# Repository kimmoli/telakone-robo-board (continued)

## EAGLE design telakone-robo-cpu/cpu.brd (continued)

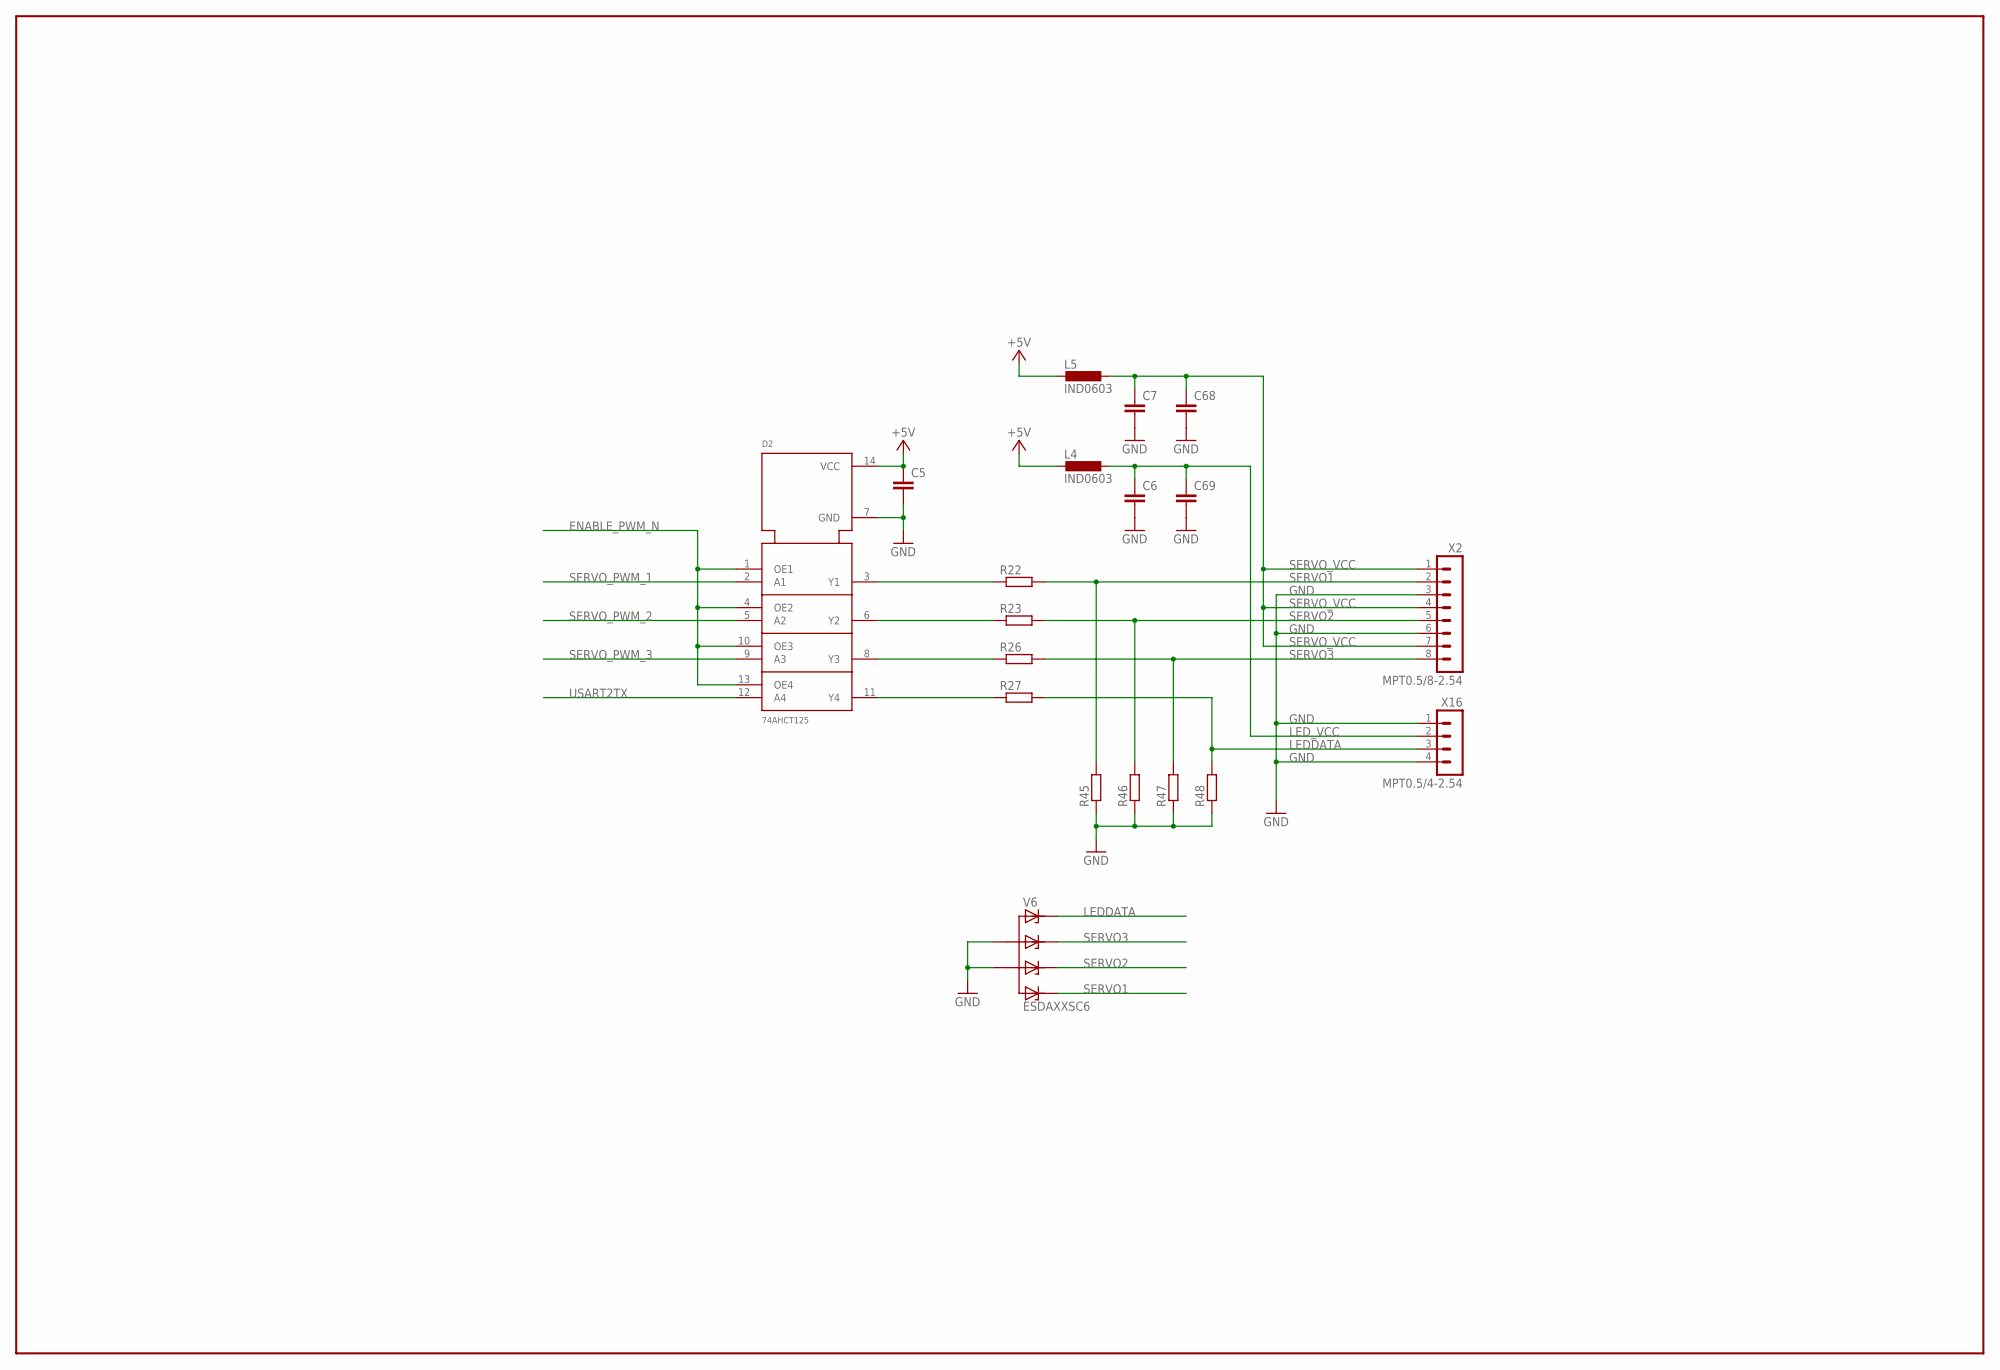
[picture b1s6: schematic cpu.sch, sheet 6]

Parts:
C5: CAP0603; OMAT_IC_2_C0603
C6, C7, C68, C69: CAP0805; OMAT_IC_2_C0805
D2: 74AHCT125; SO14
L4, L5: IND0603; OMAT_IC_2_R0603
R22, R23, R26, R27, R45, R46, R47, R48: RES0603; OMAT_IC_2_R0603
V6: ESDAXXSC6; OMAT_IC_2_SOT23-6
X2: MPT0.5/8-2.54; OMAT_IC_2_MPT0.5/8-2.54
X16: MPT0.5/4-2.54

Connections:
+5V: C5.1, D2.14 (VCC), L4.2, L5.2; also elsewhere on the board
ENABLE_PWM_N: D2.1 (OE1), D2.4 (OE2), D2.10 (OE3), D2.13 (OE4); also elsewhere on the board
GND: C5.2, C6.2, C7.2, C68.2, C69.2, D2.7 (GND), R45.1, R46.1, R47.1, R48.1, V6.2 (A), V6.5 (A1), X2.3, X2.6, X16.1, X16.4; also elsewhere on the board
LEDDATA: R27.2, R48.2, V6.1 (C), X16.3
LED_VCC: C6.1, C69.1, L4.1, X16.2
unnamed: D2.3 (Y1), R22.1
unnamed: D2.6 (Y2), R23.1
unnamed: D2.8 (Y3), R26.1
unnamed: D2.11 (Y4), R27.1
SERVO1: R22.2, R45.2, V6.6 (C3), X2.2
SERVO2: R23.2, R46.2, V6.4 (C2), X2.5
SERVO3: R26.2, R47.2, V6.3 (C1), X2.8
SERVO_PWM_1: D2.2 (A1); also elsewhere on the board
SERVO_PWM_2: D2.5 (A2); also elsewhere on the board
SERVO_PWM_3: D2.9 (A3); also elsewhere on the board
SERVO_VCC: C7.1, C68.1, L5.1, X2.1, X2.4, X2.7
USART2TX: D2.12 (A4); also elsewhere on the board

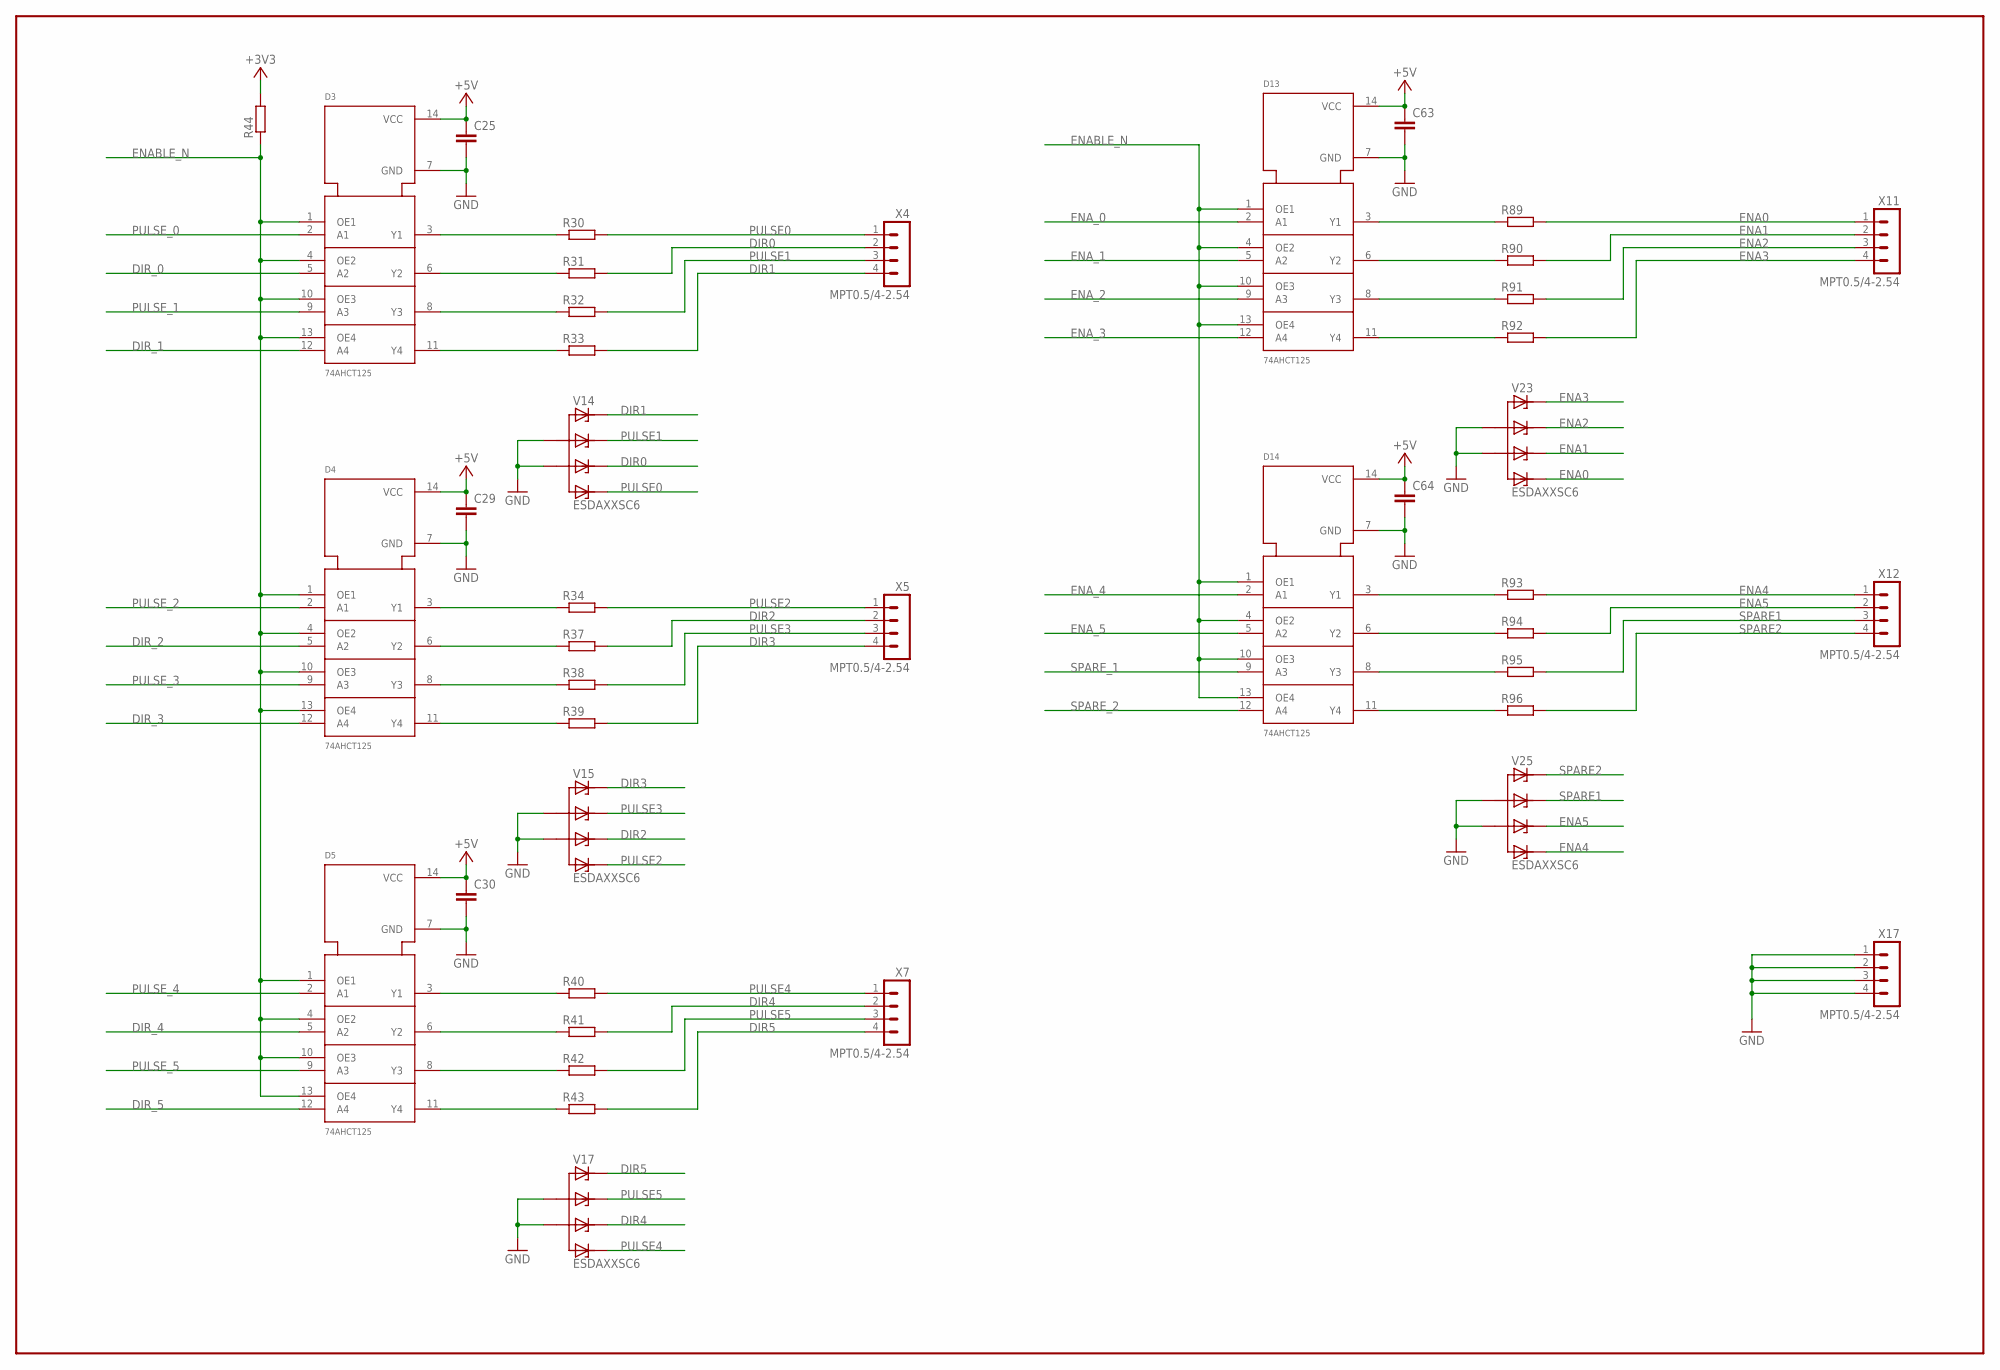
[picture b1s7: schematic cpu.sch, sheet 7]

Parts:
C25, C29, C30, C63, C64: CAP0603; OMAT_IC_2_C0603
D3, D4, D5, D13, D14: 74AHCT125; SO14
R30, R31, R32, R33, R34, R37, R38, R39, R40, R41, R42, R43, R44, R89, R90, R91, R92, R93, R94, R95, R96: RES0603; OMAT_IC_2_R0603
V14, V15, V17, V23, V25: ESDAXXSC6; OMAT_IC_2_SOT23-6
X4, X5, X7, X11, X12, X17: MPT0.5/4-2.54

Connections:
+3V3: R44.2; also elsewhere on the board
+5V: C25.1, C29.1, C30.1, C63.1, C64.1, D3.14 (VCC), D4.14 (VCC), D5.14 (VCC), D13.14 (VCC), D14.14 (VCC); also elsewhere on the board
DIR0: R31.2, V14.4 (C2), X4.2
DIR1: R33.2, V14.1 (C), X4.4
DIR2: R37.2, V15.4 (C2), X5.2
DIR3: R39.2, V15.1 (C), X5.4
DIR4: R41.2, V17.4 (C2), X7.2
DIR5: R43.2, V17.1 (C), X7.4
DIR_0: D3.5 (A2); also elsewhere on the board
DIR_1: D3.12 (A4); also elsewhere on the board
DIR_2: D4.5 (A2); also elsewhere on the board
DIR_3: D4.12 (A4); also elsewhere on the board
DIR_4: D5.5 (A2); also elsewhere on the board
DIR_5: D5.12 (A4); also elsewhere on the board
ENA0: R89.2, V23.6 (C3), X11.1
ENA1: R90.2, V23.4 (C2), X11.2
ENA2: R91.2, V23.3 (C1), X11.3
ENA3: R92.2, V23.1 (C), X11.4
ENA4: R93.2, V25.6 (C3), X12.1
ENA5: R94.2, V25.4 (C2), X12.2
ENABLE_N: D3.1 (OE1), D3.4 (OE2), D3.10 (OE3), D3.13 (OE4), D4.1 (OE1), D4.4 (OE2), D4.10 (OE3), D4.13 (OE4), D5.1 (OE1), D5.4 (OE2), D5.10 (OE3), D5.13 (OE4), D13.1 (OE1), D13.4 (OE2), D13.10 (OE3), D13.13 (OE4), D14.1 (OE1), D14.4 (OE2), D14.10 (OE3), D14.13 (OE4), R44.1; also elsewhere on the board
ENA_0: D13.2 (A1); also elsewhere on the board
ENA_1: D13.5 (A2); also elsewhere on the board
ENA_2: D13.9 (A3); also elsewhere on the board
ENA_3: D13.12 (A4); also elsewhere on the board
ENA_4: D14.2 (A1); also elsewhere on the board
ENA_5: D14.5 (A2); also elsewhere on the board
GND: C25.2, C29.2, C30.2, C63.2, C64.2, D3.7 (GND), D4.7 (GND), D5.7 (GND), D13.7 (GND), D14.7 (GND), V14.2 (A), V14.5 (A1), V15.2 (A), V15.5 (A1), V17.2 (A), V17.5 (A1), V23.2 (A), V23.5 (A1), V25.2 (A), V25.5 (A1), X17.1, X17.2, X17.3, X17.4; also elsewhere on the board
unnamed: D3.3 (Y1), R30.1
unnamed: D3.6 (Y2), R31.1
unnamed: D3.8 (Y3), R32.1
unnamed: D3.11 (Y4), R33.1
unnamed: D4.3 (Y1), R34.1
unnamed: D4.6 (Y2), R37.1
unnamed: D4.8 (Y3), R38.1
unnamed: D4.11 (Y4), R39.1
unnamed: D5.3 (Y1), R40.1
unnamed: D5.6 (Y2), R41.1
unnamed: D5.8 (Y3), R42.1
unnamed: D5.11 (Y4), R43.1
unnamed: D13.3 (Y1), R89.1
unnamed: D13.6 (Y2), R90.1
unnamed: D13.8 (Y3), R91.1
unnamed: D13.11 (Y4), R92.1
unnamed: D14.3 (Y1), R93.1
unnamed: D14.6 (Y2), R94.1
unnamed: D14.8 (Y3), R95.1
unnamed: D14.11 (Y4), R96.1
PULSE0: R30.2, V14.6 (C3), X4.1
PULSE1: R32.2, V14.3 (C1), X4.3
PULSE2: R34.2, V15.6 (C3), X5.1
PULSE3: R38.2, V15.3 (C1), X5.3
PULSE4: R40.2, V17.6 (C3), X7.1
PULSE5: R42.2, V17.3 (C1), X7.3
PULSE_0: D3.2 (A1); also elsewhere on the board
PULSE_1: D3.9 (A3)
PULSE_2: D4.2 (A1); also elsewhere on the board
PULSE_3: D4.9 (A3); also elsewhere on the board
PULSE_4: D5.2 (A1); also elsewhere on the board
PULSE_5: D5.9 (A3); also elsewhere on the board
SPARE1: R95.2, V25.3 (C1), X12.3
SPARE2: R96.2, V25.1 (C), X12.4
SPARE_1: D14.9 (A3); also elsewhere on the board
SPARE_2: D14.12 (A4); also elsewhere on the board

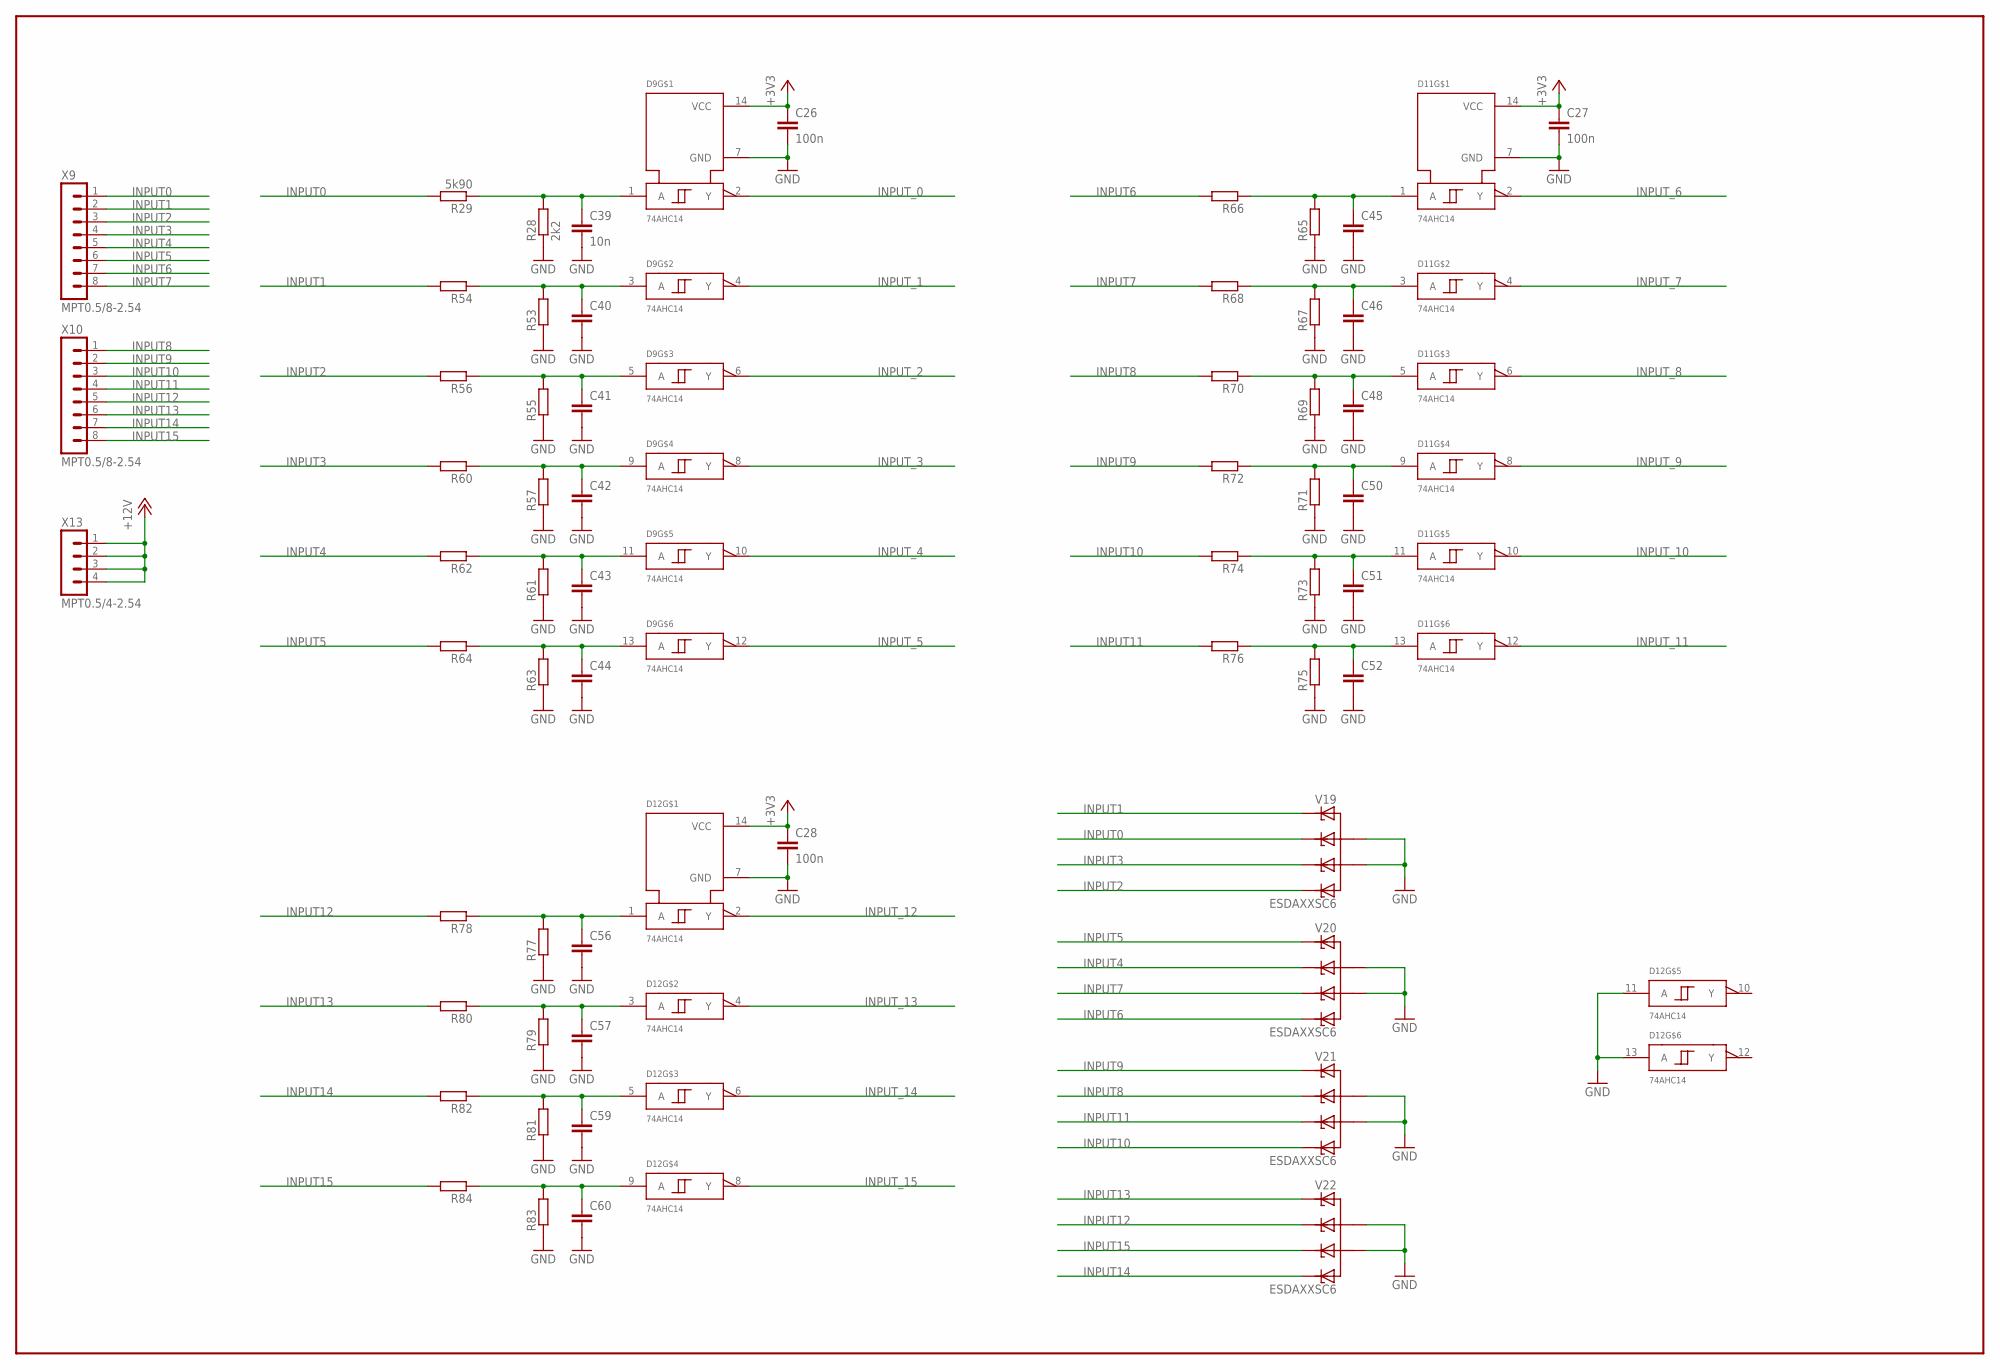
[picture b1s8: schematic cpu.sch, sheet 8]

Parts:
C26, C27, C28: 100n; C0603
C39: 10n; OMAT_IC_2_C0603
C40, C41, C42, C43, C44, C45, C46, C48, C50, C51, C52, C56, C57, C59, C60: CAP0603; OMAT_IC_2_C0603
D9, D11, D12: 74AHC14; SO14
R28: 2k2; OMAT_IC_2_R0603
R29: 5k90; OMAT_IC_2_R0603
R53, R54, R55, R56, R57, R60, R61, R62, R63, R64, R65, R66, R67, R68, R69, R70, R71, R72, R73, R74, R75, R76, R77, R78, R79, R80, R81, R82, R83, R84: RES0603; OMAT_IC_2_R0603
V19, V20, V21, V22: ESDAXXSC6; OMAT_IC_2_SOT23-6
X9, X10: MPT0.5/8-2.54; OMAT_IC_2_MPT0.5/8-2.54
X13: MPT0.5/4-2.54

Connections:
+3V3: C26.1, C27.1, C28.1, D9.14 (VCC), D11.14 (VCC), D12.14 (VCC); also elsewhere on the board
+12V: X13.1, X13.2, X13.3, X13.4; also elsewhere on the board
GND: C26.2, C27.2, C28.2, C39.2, C40.2, C41.2, C42.2, C43.2, C44.2, C45.2, C46.2, C48.2, C50.2, C51.2, C52.2, C56.2, C57.2, C59.2, C60.2, D9.7 (GND), D11.7 (GND), D12.7 (GND), D12.11 (A), D12.13 (A), R28.1, R53.1, R55.1, R57.1, R61.1, R63.1, R65.1, R67.1, R69.1, R71.1, R73.1, R75.1, R77.1, R79.1, R81.1, R83.1, V19.2 (A), V19.5 (A1), V20.2 (A), V20.5 (A1), V21.2 (A), V21.5 (A1), V22.2 (A), V22.5 (A1); also elsewhere on the board
INPUT0: R29.2, V19.3 (C1), X9.1
INPUT1: R54.2, V19.1 (C), X9.2
INPUT2: R56.2, V19.6 (C3), X9.3
INPUT3: R60.2, V19.4 (C2), X9.4
INPUT4: R62.2, V20.3 (C1), X9.5
INPUT5: R64.2, V20.1 (C), X9.6
INPUT6: R66.2, V20.6 (C3), X9.7
INPUT7: R68.2, V20.4 (C2), X9.8
INPUT8: R70.2, V21.3 (C1), X10.1
INPUT9: R72.2, V21.1 (C), X10.2
INPUT10: R74.2, V21.6 (C3), X10.3
INPUT11: R76.2, V21.4 (C2), X10.4
INPUT12: R78.2, V22.3 (C1), X10.5
INPUT13: R80.2, V22.1 (C), X10.6
INPUT14: R82.2, V22.6 (C3), X10.7
INPUT15: R84.2, V22.4 (C2), X10.8
INPUT_0: D9.2 (Y); also elsewhere on the board
INPUT_1: D9.4 (Y); also elsewhere on the board
INPUT_2: D9.6 (Y); also elsewhere on the board
INPUT_3: D9.8 (Y); also elsewhere on the board
INPUT_4: D9.10 (Y); also elsewhere on the board
INPUT_5: D9.12 (Y); also elsewhere on the board
INPUT_6: D11.2 (Y); also elsewhere on the board
INPUT_7: D11.4 (Y); also elsewhere on the board
INPUT_8: D11.6 (Y); also elsewhere on the board
INPUT_9: D11.8 (Y); also elsewhere on the board
INPUT_10: D11.10 (Y); also elsewhere on the board
INPUT_11: D11.12 (Y); also elsewhere on the board
INPUT_12: D12.2 (Y); also elsewhere on the board
INPUT_13: D12.4 (Y); also elsewhere on the board
INPUT_14: D12.6 (Y); also elsewhere on the board
INPUT_15: D12.8 (Y); also elsewhere on the board
unnamed: C39.1, D9.1 (A), R28.2, R29.1
unnamed: C40.1, D9.3 (A), R53.2, R54.1
unnamed: C41.1, D9.5 (A), R55.2, R56.1
unnamed: C42.1, D9.9 (A), R57.2, R60.1
unnamed: C43.1, D9.11 (A), R61.2, R62.1
unnamed: C44.1, D9.13 (A), R63.2, R64.1
unnamed: C45.1, D11.1 (A), R65.2, R66.1
unnamed: C46.1, D11.3 (A), R67.2, R68.1
unnamed: C48.1, D11.5 (A), R69.2, R70.1
unnamed: C50.1, D11.9 (A), R71.2, R72.1
unnamed: C51.1, D11.11 (A), R73.2, R74.1
unnamed: C52.1, D11.13 (A), R75.2, R76.1
unnamed: C56.1, D12.1 (A), R77.2, R78.1
unnamed: C57.1, D12.3 (A), R79.2, R80.1
unnamed: C59.1, D12.5 (A), R81.2, R82.1
unnamed: C60.1, D12.9 (A), R83.2, R84.1

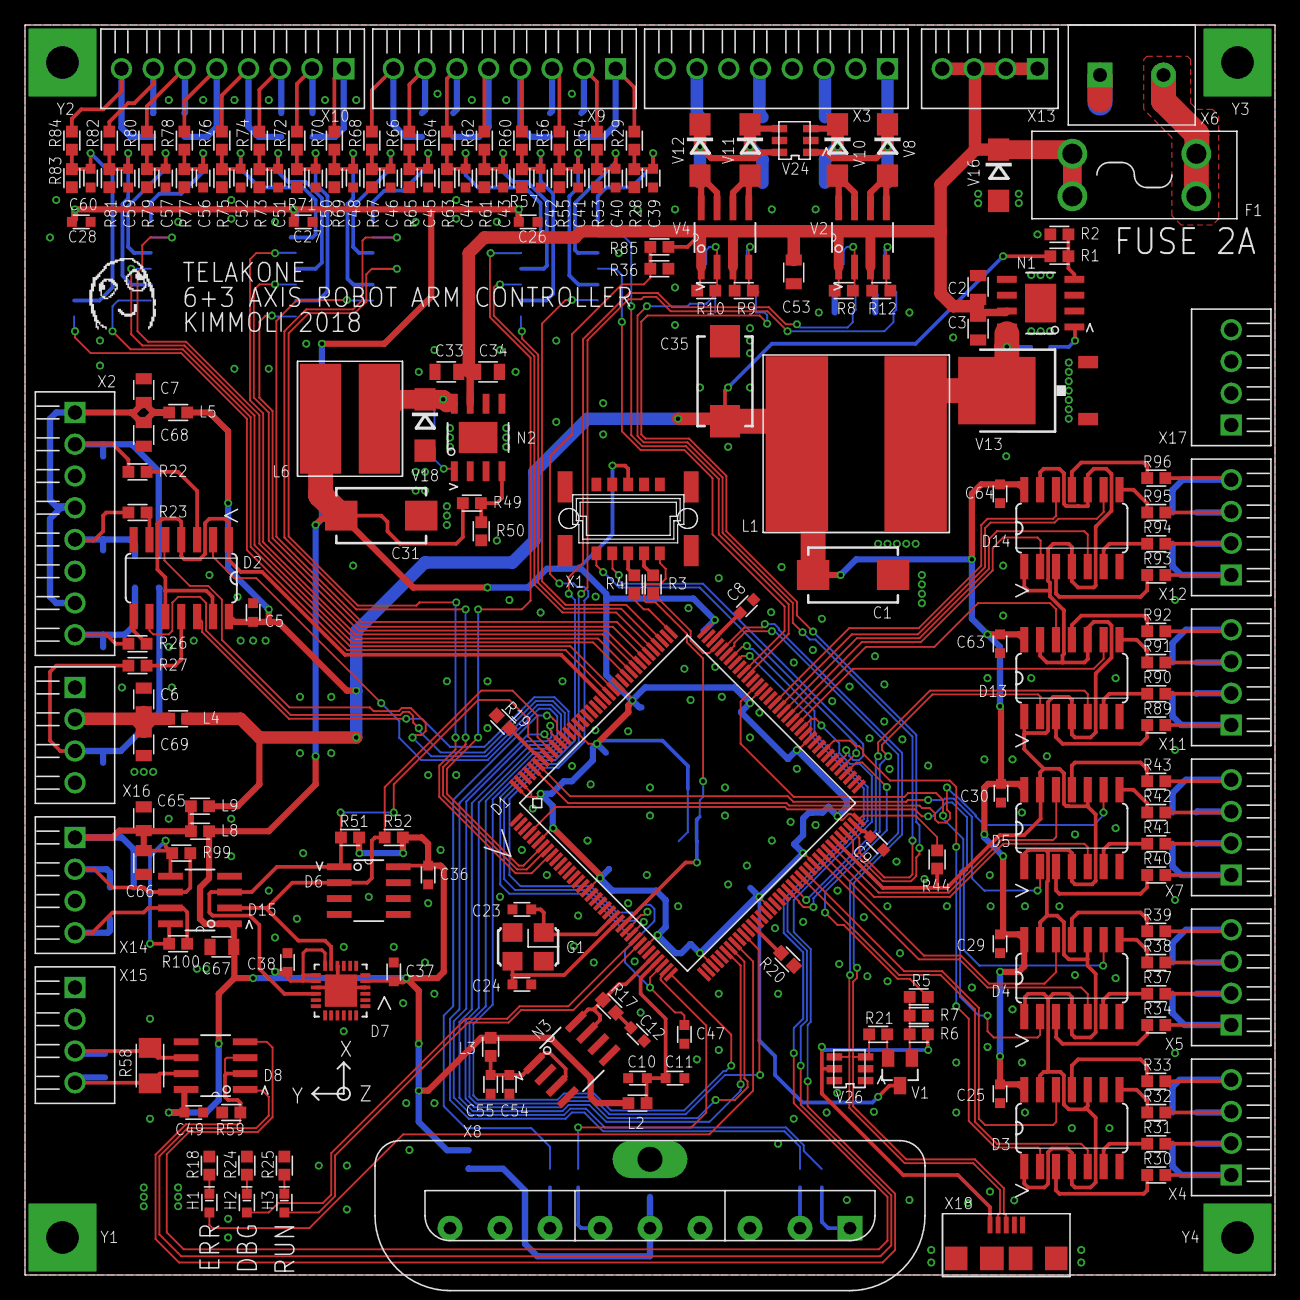
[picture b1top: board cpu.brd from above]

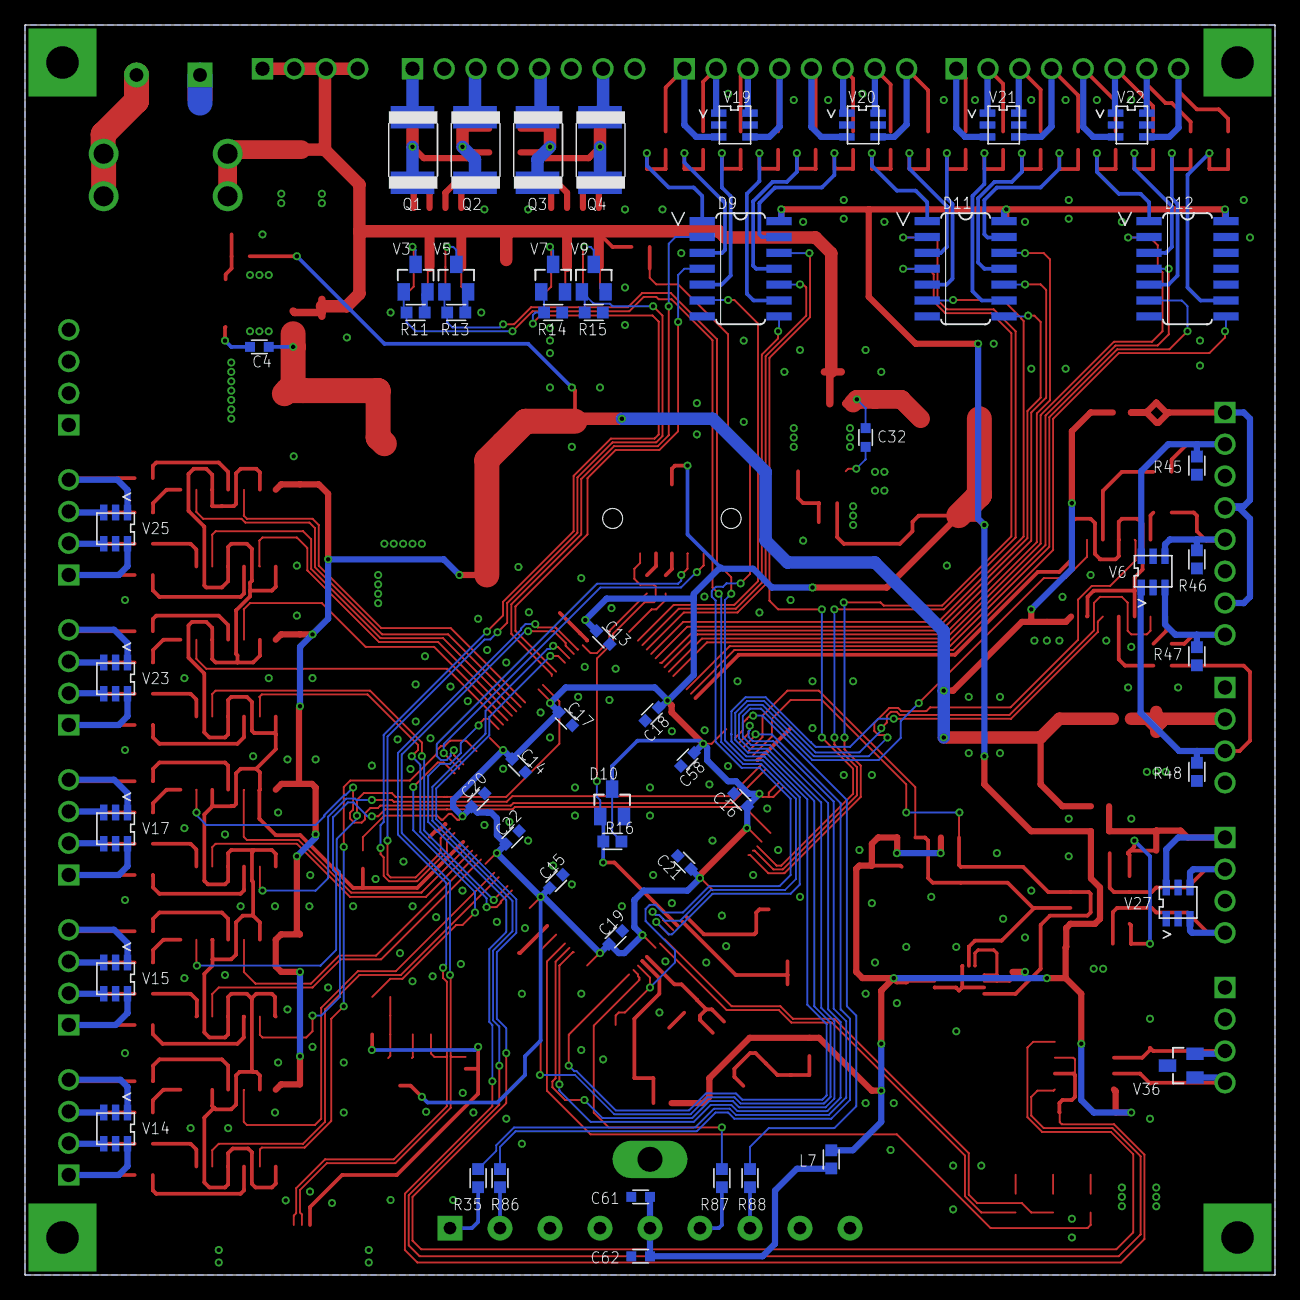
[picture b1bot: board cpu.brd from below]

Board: 2 copper layers, 100.0 x 100.0 mm, 254 parts (53 on the bottom side), 203 nets.

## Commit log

2017-12-05 Add some specs
2018-01-17 add details
2018-01-20 Add peripherals and pins
2018-01-21 debug led
2018-10-22 Add leds, usb renum, gpio directions
2018-10-22 Add RS485
2018-10-25 Add iomap, busconts
2018-12-09 add gitignore
2018-12-09 inputs
2018-12-10 input liittimet, ena outputit
2018-12-11 i2c expander yms
2018-12-11 finish schematics, rough initial placement
2018-12-12 signals routed, almost
2018-12-14 routed
2018-12-15 Final v1
2018-12-15 Gerber output, pdf
